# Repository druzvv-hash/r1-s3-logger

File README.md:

## 2026-10-23 — PowerBox now has its own R3 repository

Canonical project: [GLL R3 PowerBox](https://github.com/druzvv-hash/r3-powerbox),
branch **main**, local **C:/Projects/r3-powerbox**. Its README distinguishes Rev.A,
Rev.B candidate and user-reported physical checks. Existing hardware files were
copied byte-for-byte; PowerBox history was filtered with an original/new commit
map. Previously local RevB/manufacturing evidence is now tracked privately.
No circuit change, new hardware test or manufacturing approval is implied.
The old r3-powerbox-routing worktree and R1 branch remain historical references;
do not start new PowerBox development there. This supersedes older location and
local-only status below. See the new repository's docs/MIGRATION_2026-10-23.md.

<!-- External project memory audit - 2026-10-23 -->
**Current technical handoff:** [NOTES](NOTES.md) · [WORK_REPORT](WORK_REPORT.md) ·
[evidence and open issues](docs/PROJECT_MEMORY.md). Read [AGENTS](AGENTS.md)
before work. Version/status text below may describe older milestones; the dated
memory entry distinguishes current source, reported deployment and untested work.

# R1-S3 Logger

**[Посібник екосистеми: схеми, підключення та інструкції](../lily-logger-r3/docs/manual/README.uk.md)** — актуальний спільний вхід для R3, R1, CANBox і Viewer.

**English** | [Українська](README.uk.md)

Rebuilding Logger R1 around **ESP32-S3 + INA228**. Current firmware: **PANEL v0.36-can-live-dev**, with USB/Wi-Fi Start/Stop controls, integer 1–300 Hz measurements with presets and manual input, a 30/60 FPS live chart and explicit draft/apply/save settings. Sessions flow through a PSRAM FIFO into checked block writes on microSD. The encoder remains a no-GPIO stub. [Recording guide](docs/P5_RECORDING.md).

CAN tab: shared live/CBX playback/finite transmit workspace, using CANBox USB or
Wi-Fi directly. BLE remains service-only. [CAN guide](../GLL%20CANBox/docs/CAN_WORKSPACE.uk.md).

INA228 averaging/conversion controls and 10/30/60 s chart navigation: [guide](docs/INA228_PANEL.md).
**R3 ecosystem:** saved authenticated association, boot reconnect, coarse RTC
correction while idle and optional remote Start/Stop through R3's `/ecosystem`
page are implemented and host-tested. A [bounded two-board bench passed](docs/ECOSYSTEM_ACCEPTANCE_2026-09-09.md)
for saved permissions, coarse RTC correction, selected control and reboot recovery. Save
time-only or explicitly enable recording permission. New files use CSV v2 with
static group/RTC provenance, preserving v1 reading. [Operator guide](docs/ECOSYSTEM_CONTROL.md).

**Device UI:** run [device_ui/start.cmd](device_ui/start.cmd) with the board on native USB (COM9 on this PC),
or join the logger's Wi-Fi AP and open 192.168.4.1. Credentials are shown in the USB
panel's Diagnostics tab. [Test-panel guide](docs/P4A_TEST_PANEL.md).

**SD files:** the **Файли SD** tab lists folders and downloads existing files through
USB or Wi-Fi, without removing the card. [File transfer guide](docs/SD_DOWNLOADS.md).
The scrolling explorer includes search, sorting and automatic full-folder loading.
[Measured rate/noise limits](docs/RATE_BENCHMARK.md) distinguish usable control from
the experimental recording ceiling; v0.22 adds explicit [1–300 Hz profiles](docs/MEASUREMENT_RATES.md) with visible speed/noise tradeoffs.

## Hardware

- ESP32-S3-WROOM-2-N32R16V (reported marking MCN32R16V): 32 MB Octal Flash, 16 MB Octal PSRAM.
- Shared I²C bus: SDA GPIO8, SCL GPIO9, 100 kHz; INA228 `0x40`, SH1106G 128×64 OLED `0x3C`, 24C32 EEPROM `0x50`, DS3231 RTC `0x68`.
- SPI SD: CS GPIO10, MOSI GPIO11, SCK GPIO12, MISO GPIO13.
- INA228 ALERT: GPIO14. External shunt: owner-confirmed 60 mV / 400 A (150 microohms).
- OLED rotation: 180°. The current bench uses direct ESP32-S3 USB Serial/JTAG on COM9.

See the [pin map](hardware/pinmap.md). Board revision and SD module circuitry remain to be recorded.

Selected local control: [Bourns PEC11R-4220F-S0024](hardware/encoder.md), not yet installed. Physical and web controls will share one device state.

## Verified status

| Component | Result |
|---|---|
| Flash / PSRAM | Detected; no memory stress test performed |
| I²C | Four expected addresses responding in repeated scans without bus errors |
| SD | 10 MHz write, close, remount and exact readback PASS; output files checked on a PC |
| OLED | SH1106G 128×64 image and 180° rotation confirmed by the owner |
| EEPROM | Owner confirmed EEP PASS: backup, sample write, restore and full-image comparison |
| RTC | Browser UTC synchronization verified; OSF=0, tick PASS; retention checked after owner-reported power disconnection |
| INA228 | Fresh ADC and owner-reported voltage comparison established; independent current calibration and active ALERT pending |

Native USB flashing, full-image verification and console operation are confirmed. Use direct USB going forward; the cause of intermittent CP210x failures remains unproven.

## VS Code / PlatformIO

Open the repository root in VS Code with PlatformIO IDE installed. Dependencies are pinned to `espressif32@6.12.0` (Arduino 2.0.17), `Adafruit SH110X@2.1.12` and `NimBLE-Arduino@1.4.3`.

```sh
pio run
```

The default environment is `esp32-s3-usb`: direct USB Serial/JTAG with the console enabled. This R1 is COM9; confirm device identity before flashing (CANBox is COM11). Close the UI bridge / Serial Monitor before uploading. Port numbers may change on another PC.

```sh
pio run -e esp32-s3-usb -t upload --upload-port COM9
pio device monitor -e esp32-s3-usb -p COM9
```

`esp32-s3-uart-manual` retains the BOOT + RESET fallback (manual RESET after upload). `esp32-s3` retains the old UART profile; native USB is the normal workflow. The explicit `esp32-s3-service` build enables the original SD/EEPROM write tests; ordinary builds exclude them.

## Current behavior and migration

Normal boot reads the SD root and checks two complete EEPROM reads, then displays live voltage/current. It creates no SD test files and writes no EEPROM patterns. `SD READ / SAVED` indicates readable SD and matching persisted settings; UNSAVED means explicit saving is needed. The explicit [RTC sync](docs/rtc-sync.md) command remains available; saved R3 enrollment also permits automatic fresh RTC correction while idle. INA228 uses timed 1–300 Hz acquisition. Explicit START creates a session; STOP drains, verifies and closes it before publishing the CSV.

[3 A / 3 V load acceptance](docs/LOAD_TEST_2026-09-08.md): all three rates passed without missed samples or I2C errors; 40 verified USB downloads passed alongside 100 Hz acquisition. v0.17 fixes delayed panel-state publication found during these tests.

The [PSRAM FIFO and block-buffer foundation](docs/BUFFERING_AND_REUSE.md) is implemented and host-tested. Boot reserves the configured sample budget in PSRAM plus 8 KiB internal SD staging; the recorder now uses these buffers after explicit Start. P4a now has a working web test panel on core 0 and a hardware command owner on core 1. [P4b live acquisition](docs/P4B_LIVE_ACQUISITION.md) now uses timed INA conversions, chunked OLED transfers and batched PSRAM preview. [P5 session files](docs/P5_RECORDING.md) are implemented; local menus remain.

[P0 baseline and backup evidence](docs/P0_BASELINE.md). P1 contracts: [settings/EEPROM](docs/CONFIG_SCHEMA.md), [self-contained CSV](docs/FILE_FORMAT.md), [viewer compatibility](docs/VIEWER_COMPATIBILITY.md). Run host checks with `python -m unittest discover -s tests -v` (Python 3.10+; firmware-core tests also need a native C++ compiler). P2 viewer is implemented: launch `viewer/start.cmd` or `python viewer/server.py`. [Viewer guide](viewer/README.md) · [P2 results](docs/P2_VIEWER.md). P3 settings/EEPROM are implemented: [commands and evidence](docs/P3_SETTINGS.md). P5 connects acquisition to session recording, checkpoints and rotation; physical acceptance and limits are in the recording guide. The owner deferred remaining R5 analysis/plugins until real logger files exist. The current viewer is a data-reading foundation, not a feature-complete R5 replacement.

## Repository guide

- [BLE link controls](docs/BLE_LINK.md): authenticated pairing and explicit saved permission through **BLE · R3**. The [v0.24 two-board bench](docs/ECOSYSTEM_ACCEPTANCE_2026-09-09.md) verifies control and recovery within documented limits; extended qualification and the earlier 300 Hz signal-quality question remain open.
- [Ecosystem control](docs/ECOSYSTEM_CONTROL.md): time-only/remote permission, ON/OFF/FORGET, boot RTC correction and selected R3 control.
- [Ecosystem synchronization](docs/ECOSYSTEM_TIME_SYNC.md): R3 / R1-S3 / CAN architecture; [CSV v2](docs/FILE_FORMAT_V2.md) has static provenance, while precise sample alignment and the CAN adapter remain pending.
- [firmware/](firmware/README.md): Arduino test firmware and GPIO constants.
- [hardware/](hardware/README.md): hardware notes and pin map.
- [Bring-up plan and results](docs/bring-up.md).
- [SD serial evidence](docs/sd-test-v0.2-serial.txt).
- [Project context](docs/project-context-review.md): relevant findings from earlier logger work.
- [Ukrainian owner notes](docs/uk/README.md): historical bench notes and local workspace review.

See the staged plan below for remaining acquisition, calibration, ALERT and recording acceptance work.

Legacy recovery: [R1 firmware and viewer review](docs/legacy-r1-analysis.md).

- [Migration journal](docs/R1_MIGRATION.md): migration stages, decisions and dated hardware evidence.

- [Engineering plan](docs/R1_S3_PLAN.md): architecture, EEPROM, self-contained recording and cross-version viewer roadmap.

## CANBox fallback (experimental)

The direct CANBox control adapter and panel are implemented in the working tree.
R1 flashing and the two-board BLE acceptance are pending a manual BOOT/RESET.
See [CANBox fallback status and procedure](docs/CANBOX_FALLBACK.md).

The owner confirmed that the R1 SD card was removed during the CANBox bench. The observed SD FAIL therefore does not establish an SD fault; recheck after reinsertion.

Deployed update: **0.28-canbox-dev** adds an always-visible CANBox status and controls, including unknown/offline and pending states. Native USB deployment and live CANBox readiness/authorization verified.

## CANBox clock update 0.29

Deployed: the connected R1 supplies its valid, fresh RTC calendar to CANBox.
START requires clock_synced; STOP remains available. Live synchronization
passed; the new SD-file acceptance test awaits card reinsertion in CANBox.
See `C:\Projects\GLL CANBox\docs\CLOCK_SYNC_2026-09-15.uk.md`.

**CANBox + R1:** [Спільний запис / linked Start and Stop](docs/LINKED_RECORDING.uk.md) — перемикач біля старту CANBox, одна група сесій, підтверджений стан обох пристроїв.

Wi-Fi firmware updates: [Browser OTA](docs/OTA.md).

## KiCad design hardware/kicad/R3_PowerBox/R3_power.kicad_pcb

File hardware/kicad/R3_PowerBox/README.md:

# R3 PowerBox

Editable KiCad 10 project for the R3 power module. The schematic uses one root
page and ten functional child sheets so battery/BMS, charger/power-path,
user system-power control, primary converters, isolation, LDOs, INA bipolar power and connectors can be
reviewed independently.

## Open

Open `R3_power.kicad_pro` in KiCad 10. The canonical schematic is
`R3_power.kicad_sch`; the PCB file is `R3_power.kicad_pcb`.

## Directory layout

- `R3_power.kicad_pro` — KiCad project settings;
- `R3_power.kicad_sch` — power schematic;
- `R3_power.kicad_pcb` — PCB workspace;
- `libraries/` — project-local symbols and source libraries;
- `footprints/` — project-local provisional footprints;
- `docs/` — design decisions, checks, and transfer notes;
- `bom/` — KiCad-exported BOM plus sourcing/review notes;
- `legacy/` — read-only KiCad 5 source retained for migration reference;
- `tools/` — reproducible schematic generator and its setup notes;
- `manufacturing/` — release outputs only after schematic/PCB review;
- `reports/` — ERC/DRC reports generated during checks.

## Safety and design status

- The board is a unified 2S Li-ion power-management design. The preliminary
  system range is 6.0-8.4 V; there is no intermediate 2S-to-9 V converter.
- J1 is retained as a protected service/bench charger input. USB-C is the
  primary external input; STUSB4500 implements 5/9/12 V negotiation with
  12 V/2 A preferred and a boot-safe 0.50 A charger default.
- `DGND` and `GND_ISO` are separate galvanic domains and must never be joined.
- SW1/Q4 disconnect only `VSYS_MAIN`; BMS, PD and charging remain active while
  R3 is off. SW2 is the separate QON ship/wake/service control.
- The present files are an engineering prototype, not a manufacturing release.
- Q2/Q3, F1/F2/F3 and the dual-NTC strategy are selected for Rev.A. Battery
  chemistry/configuration, hot-current validation and PD NVM compliance remain
  open before ordering a PCB.
- The PCB contains a 160 x 80 mm outline, four spatial zones, an isolation
  keepout on all four copper layers, six NPTH M3 mounting holes, optional
  primary/isolated B2B headers and final pre-routing component placement. It
  has no routing or vias.
- KiCad ERC has zero errors. Remaining generator-related warnings and the visual
  review limitations are recorded in `docs/VERIFICATION.md`.

Start with [the current power review](R3_POWER_REVIEW.md) and
[battery architecture](R3_BATTERY_POWER_ARCHITECTURE.md), then see the compact
[design notes](docs/R3_power_module_design.md) and
[verification status](docs/VERIFICATION.md). Placement images are in
`reports/R3_power_preliminary_placement.png` and
`reports/R3_power_zone_isolation_annotated.png`; mechanical stack dimensions
and views are in [the B2B interface note](docs/R3_BOARD_TO_BOARD_INTERFACE.md).

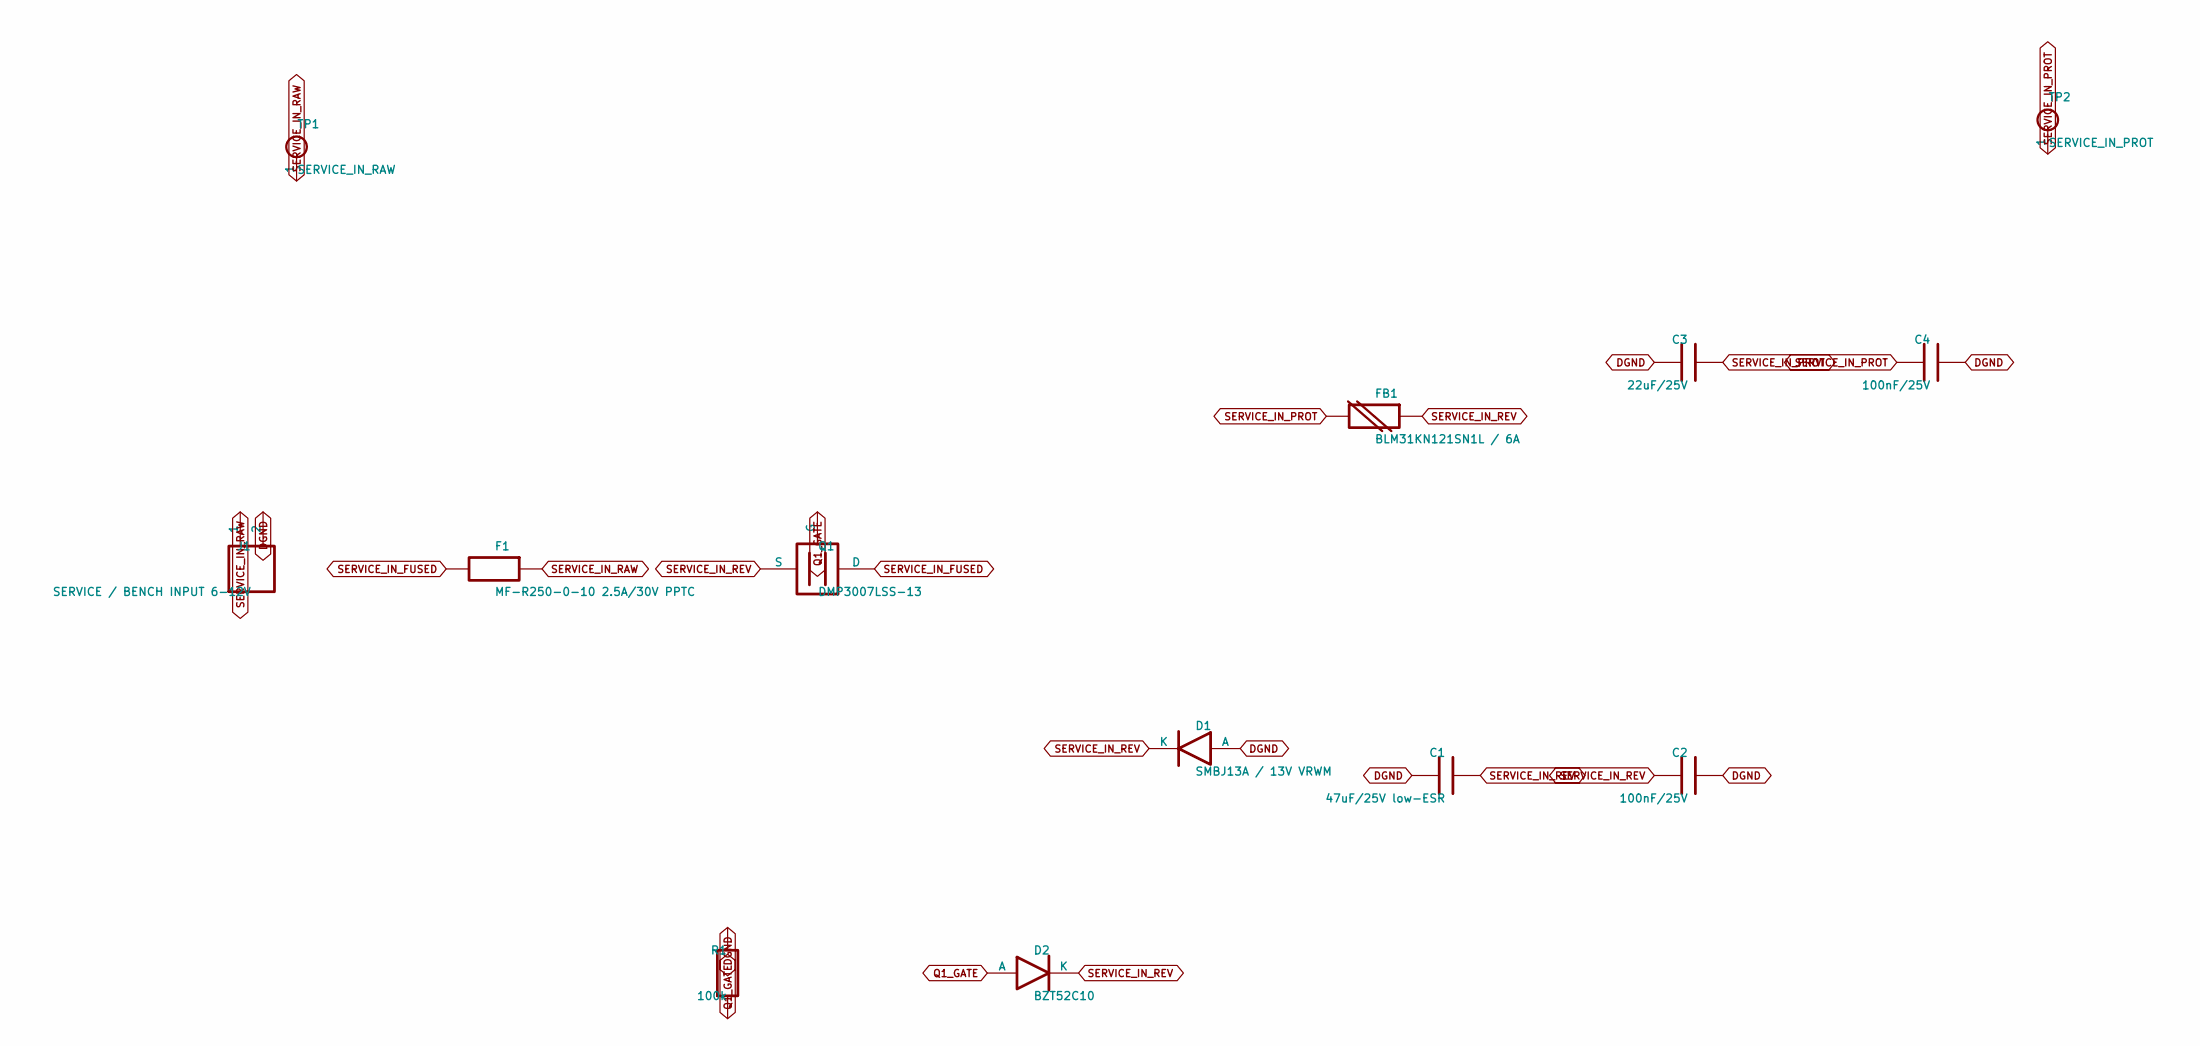
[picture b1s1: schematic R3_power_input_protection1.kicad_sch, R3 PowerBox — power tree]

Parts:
C1: 47uF/25V low-ESR; CP_Elec_6.3x5.8
C2, C4: 100nF/25V; C_0603_1608Metric
C3: 22uF/25V; C_1206_3216Metric
D1: SMBJ13A / 13V VRWM; D_SMB
D2: BZT52C10; D_SOD-123
F1: MF-R250-0-10 2.5A/30V PPTC; Fuse_PTC_MF-R250
FB1: BLM31KN121SN1L / 6A; L_1206_3216Metric_Pad1.22x1.90mm_HandSolder
J1: SERVICE / BENCH INPUT 6-12V; Molex_Micro-Fit_3.0_43650-0200_1x02_P3.00mm_Horizontal
Q1: DMP3007LSS-13; DMP3007LSS_SO8_LOGICAL
R1: 100k; R_0603_1608Metric
TP1: SERVICE_IN_RAW; TestPoint_Plated_Hole_D2.0mm
TP2: SERVICE_IN_PROT; TestPoint_Plated_Hole_D2.0mm

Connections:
DGND: C1.2, C2.2, C3.2, C4.2, D1.2 (A), J1.2, R1.2; also elsewhere on the board
Q1_GATE: D2.2 (A), Q1.1 (G), R1.1
SERVICE_IN_FUSED: F1.2, Q1.3 (D)
SERVICE_IN_PROT: C3.1, C4.1, FB1.2, TP2.1; also elsewhere on the board
SERVICE_IN_RAW: F1.1, J1.1, TP1.1
SERVICE_IN_REV: C1.1, C2.1, D1.1 (K), D2.1 (K), FB1.1, Q1.2 (S)

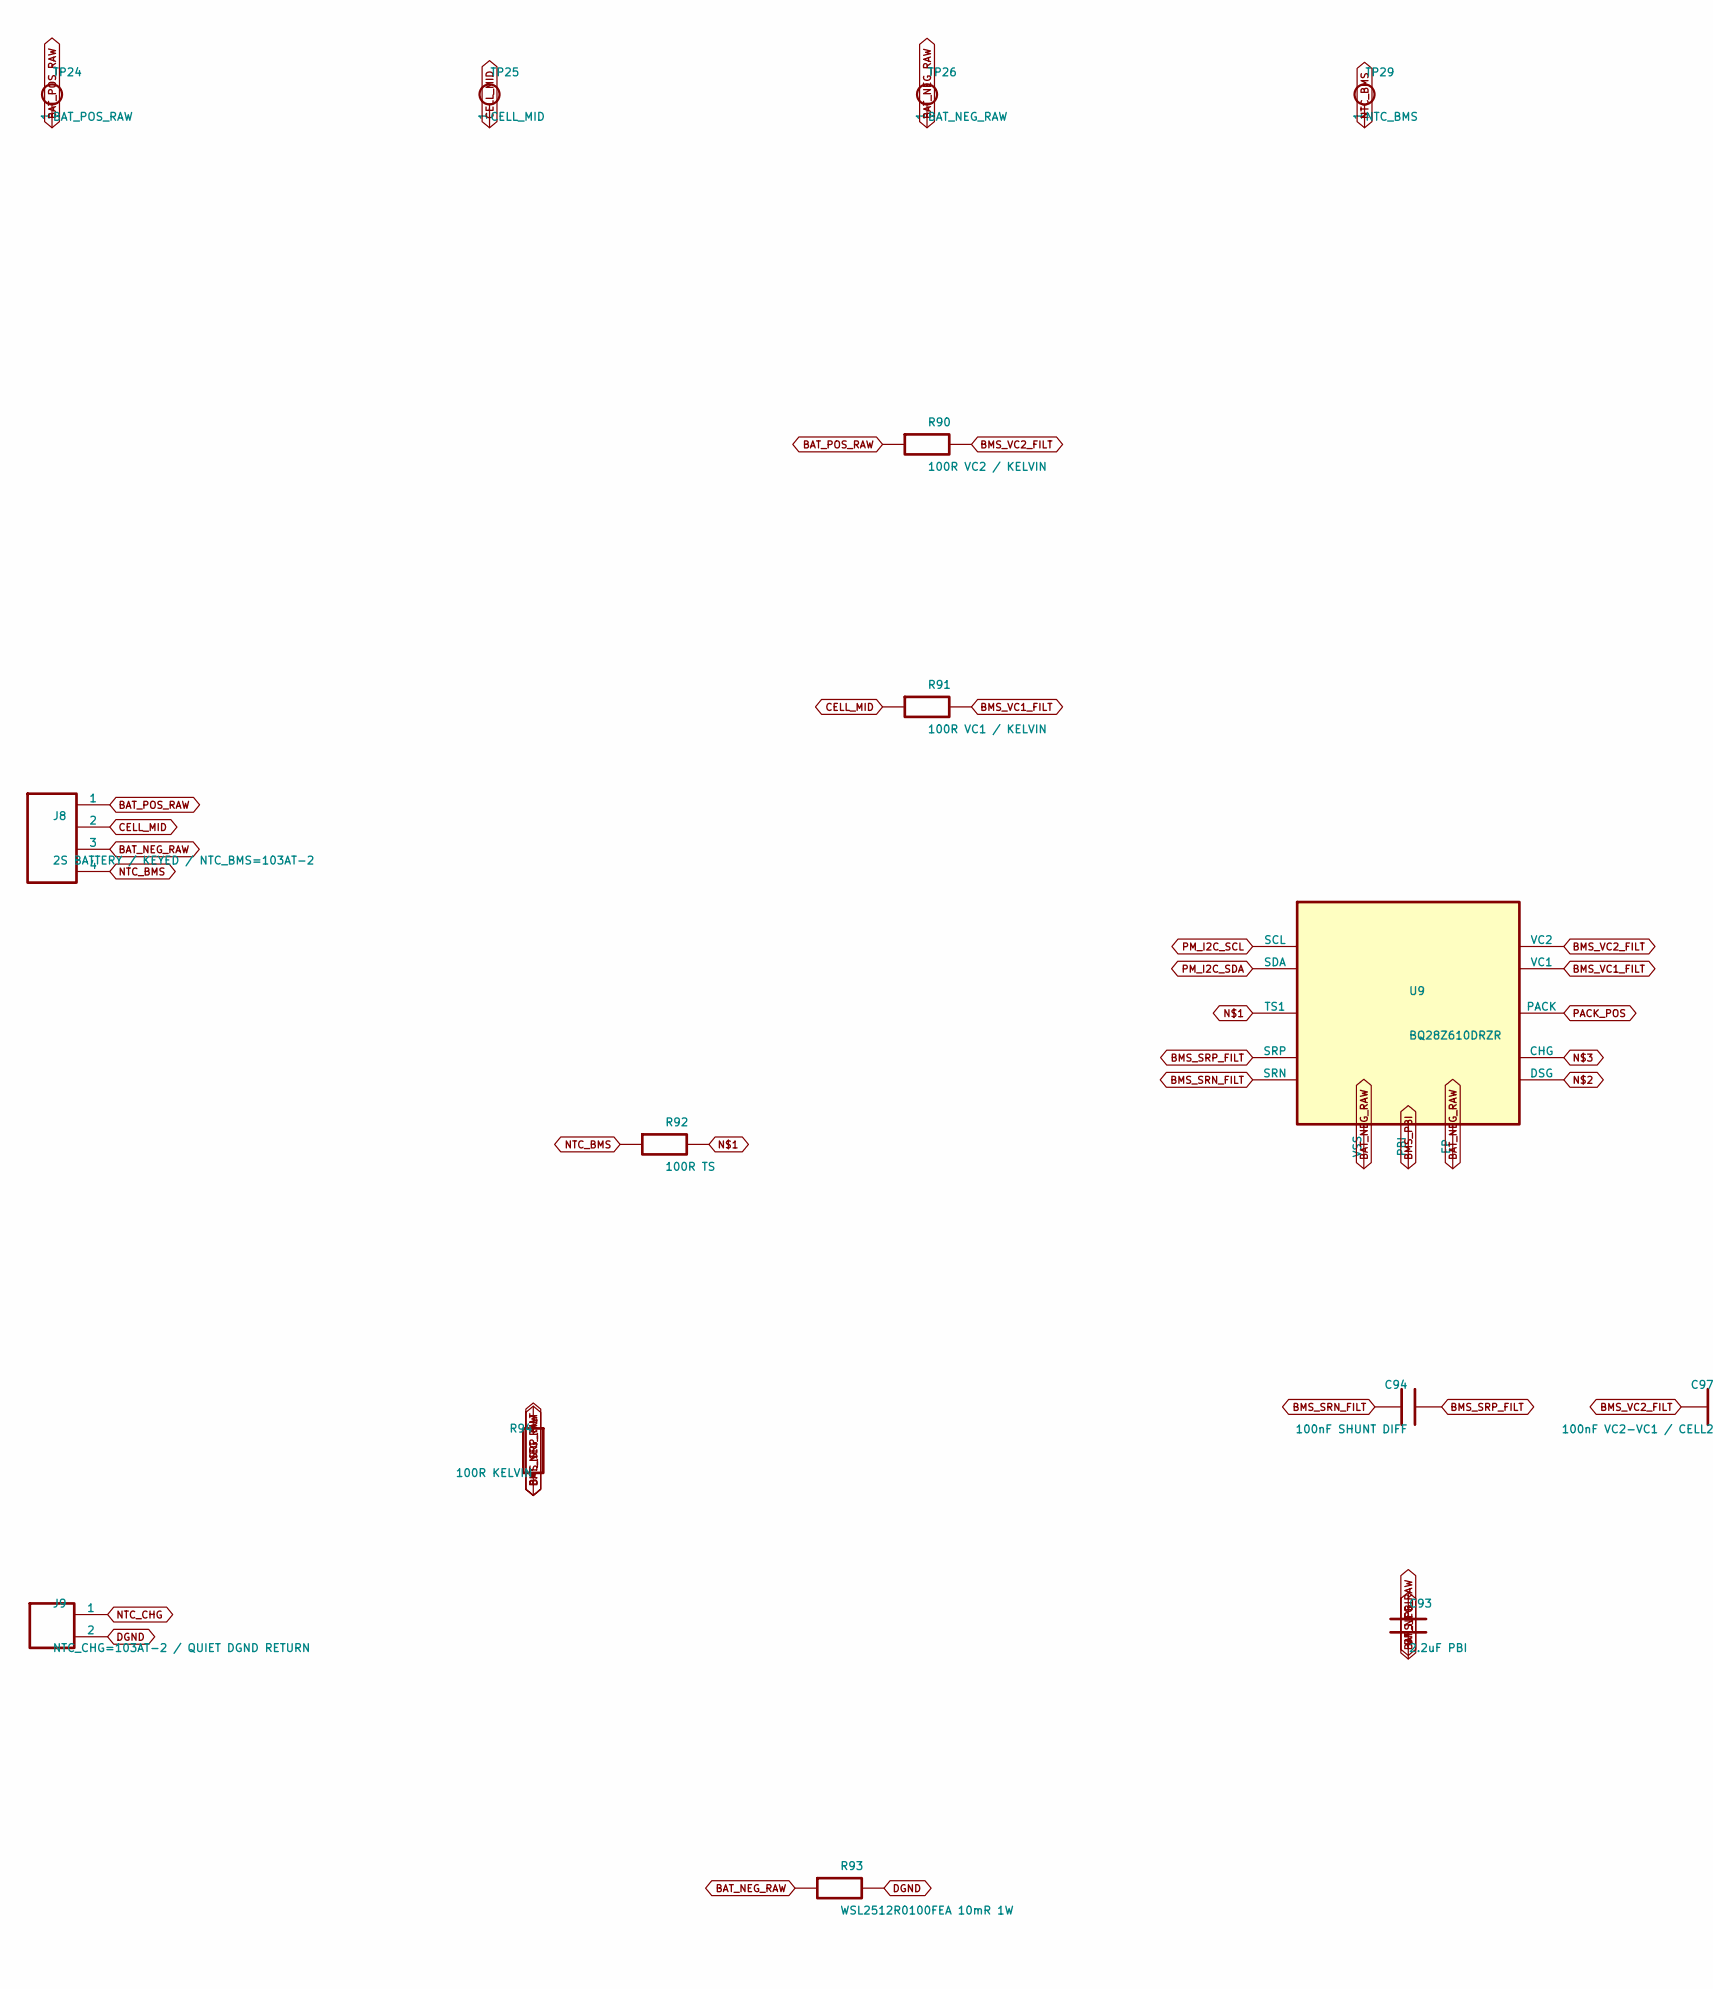
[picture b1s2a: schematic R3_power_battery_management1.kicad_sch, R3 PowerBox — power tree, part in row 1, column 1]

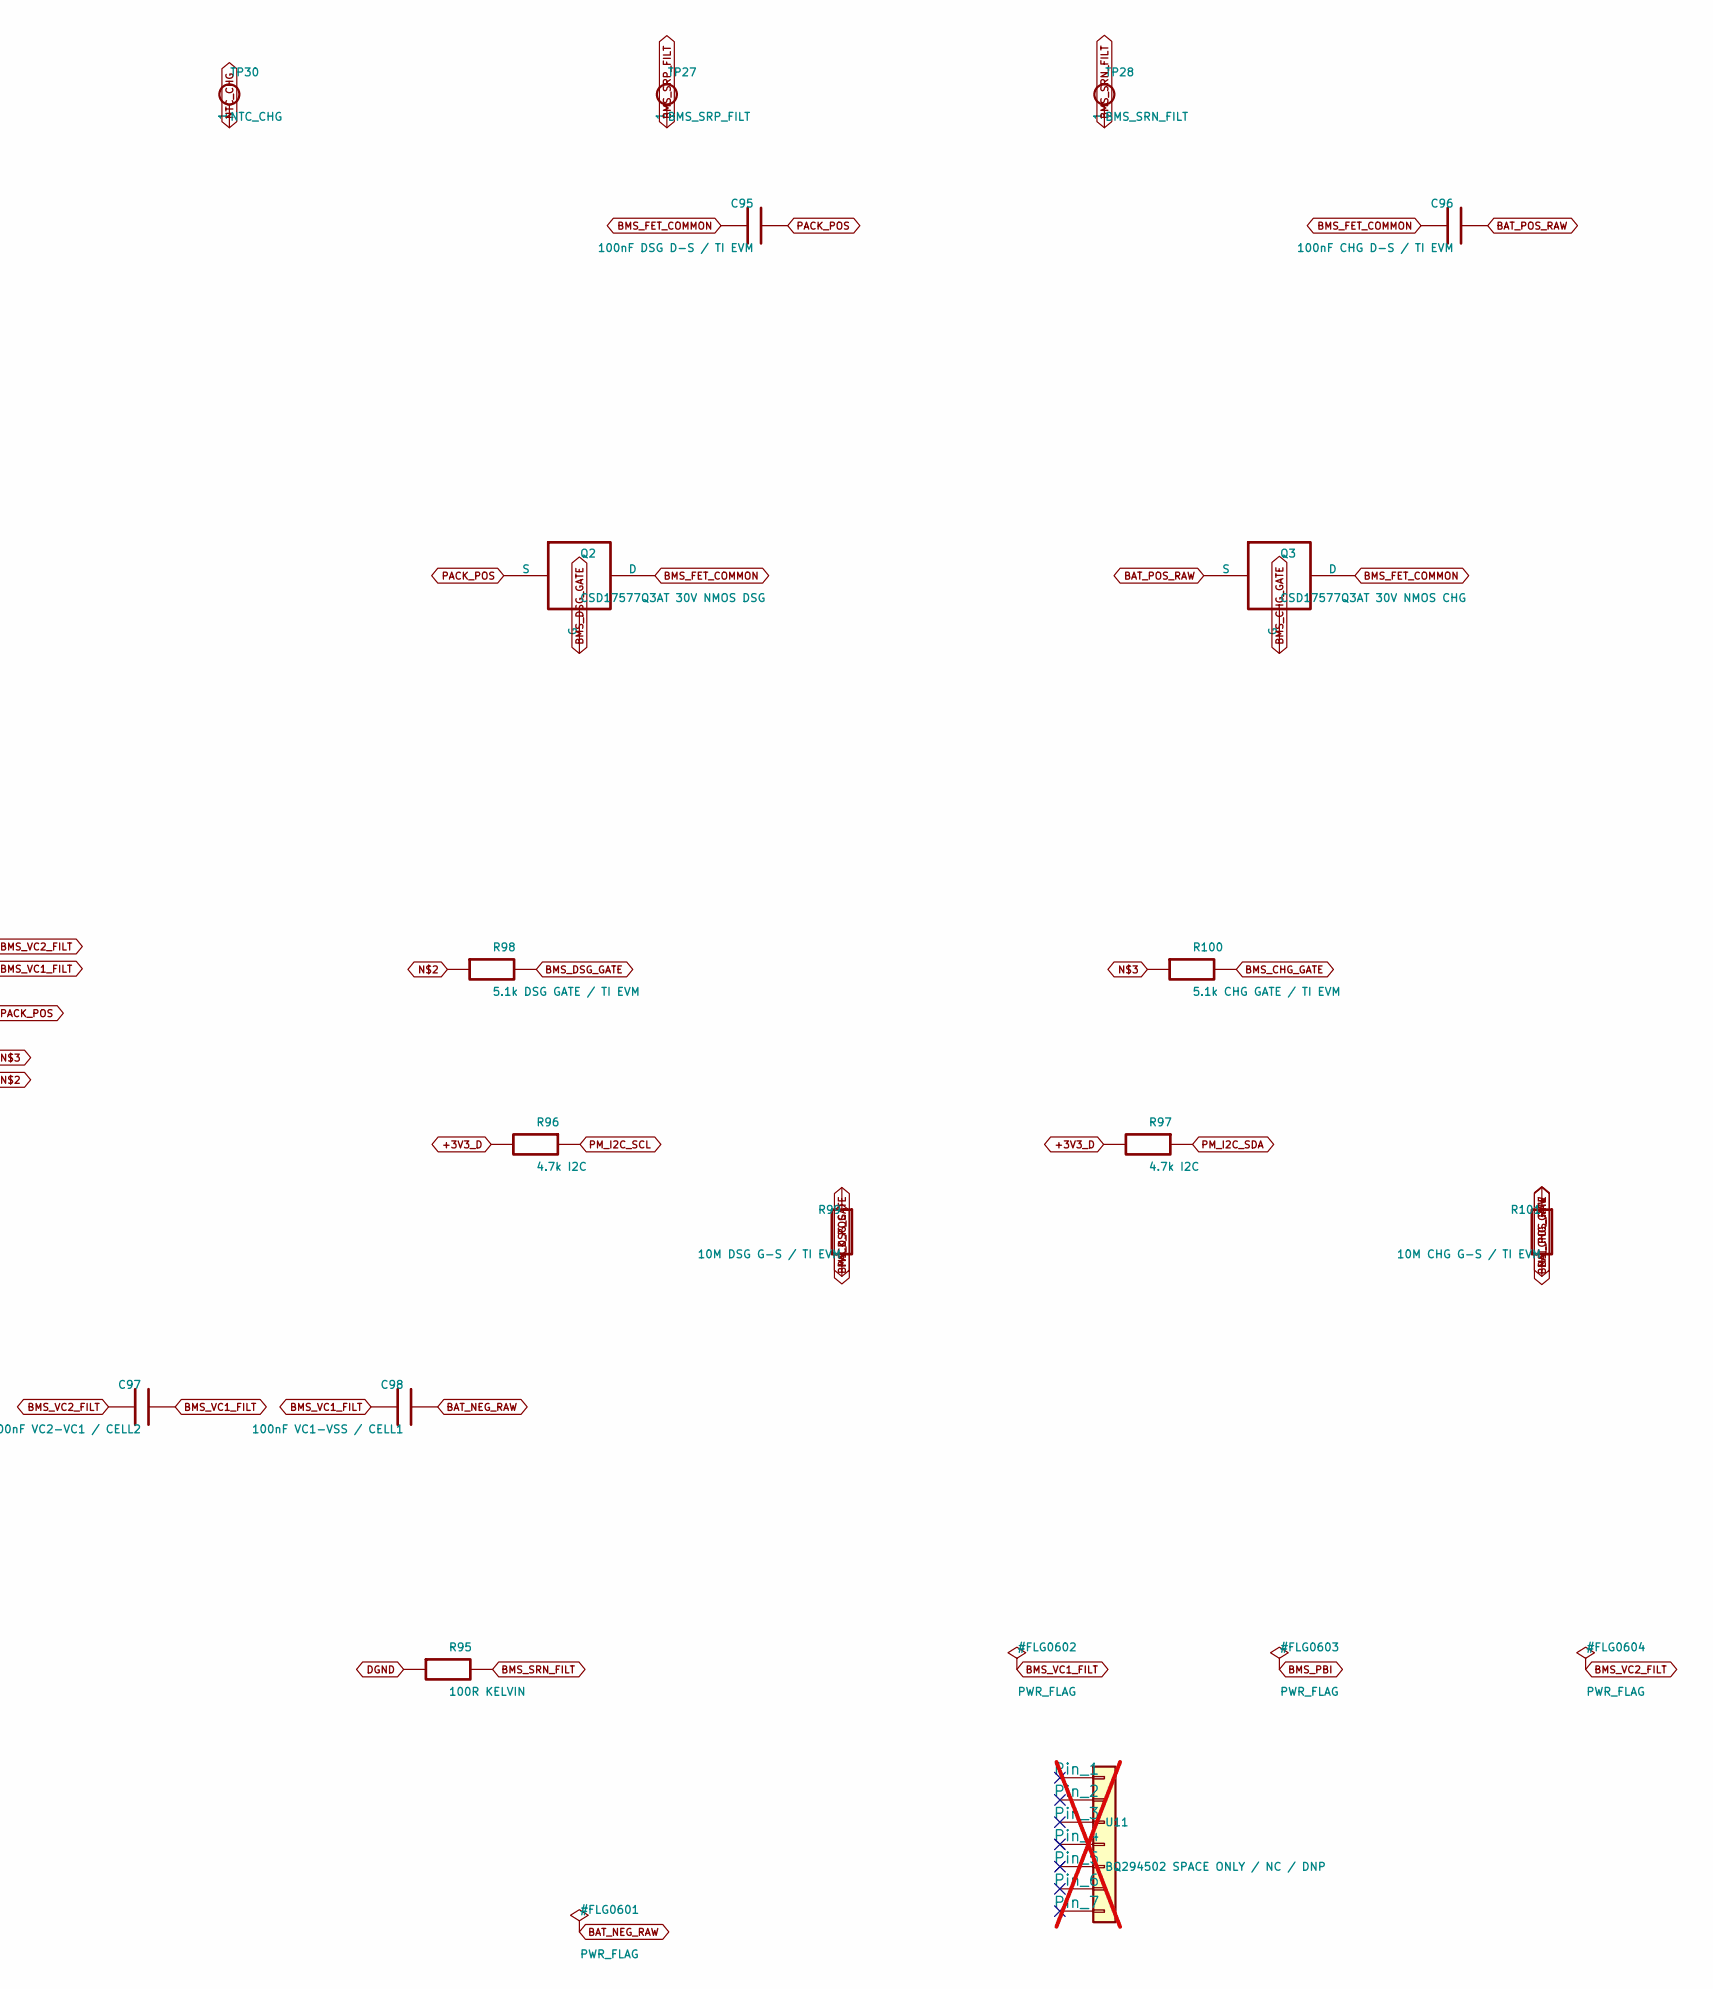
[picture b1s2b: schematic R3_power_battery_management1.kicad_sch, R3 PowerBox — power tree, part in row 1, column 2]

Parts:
C93: 2.2uF PBI; C_0603_1608Metric
C94: 100nF SHUNT DIFF; C_0603_1608Metric
C95: 100nF DSG D-S / TI EVM; C_0603_1608Metric
C96: 100nF CHG D-S / TI EVM; C_0603_1608Metric
C97: 100nF VC2-VC1 / CELL2; C_0603_1608Metric
C98: 100nF VC1-VSS / CELL1; C_0603_1608Metric
J8: 2S BATTERY / KEYED / NTC_BMS=103AT-2; Molex_Micro-Fit_3.0_43650-0400_1x04_P3.00mm_Horizontal
J9: NTC_CHG=103AT-2 / QUIET DGND RETURN; Molex_Micro-Fit_3.0_43650-0200_1x02_P3.00mm_Horizontal
Q2: CSD17577Q3AT 30V NMOS DSG; CSD17577Q3A_VSON-8_3.3x3.3mm
Q3: CSD17577Q3AT 30V NMOS CHG; CSD17577Q3A_VSON-8_3.3x3.3mm
R90: 100R VC2 / KELVIN; R_0603_1608Metric
R91: 100R VC1 / KELVIN; R_0603_1608Metric
R92: 100R TS; R_0603_1608Metric
R93: WSL2512R0100FEA 10mR 1W; R_2512_6332Metric_Pad1.40x3.35mm_HandSolder
R94, R95: 100R KELVIN; R_0603_1608Metric
R96, R97: 4.7k I2C; R_0603_1608Metric
R98: 5.1k DSG GATE / TI EVM; R_0603_1608Metric
R99: 10M DSG G-S / TI EVM; R_0603_1608Metric
R100: 5.1k CHG GATE / TI EVM; R_0603_1608Metric
R101: 10M CHG G-S / TI EVM; R_0603_1608Metric
TP24: BAT_POS_RAW; TestPoint_Plated_Hole_D2.0mm
TP25: CELL_MID; TestPoint_Plated_Hole_D2.0mm
TP26: BAT_NEG_RAW; TestPoint_Plated_Hole_D2.0mm
TP27: BMS_SRP_FILT; TestPoint_Pad_D1.0mm
TP28: BMS_SRN_FILT; TestPoint_Pad_D1.0mm
TP29: NTC_BMS; TestPoint_Plated_Hole_D2.0mm
TP30: NTC_CHG; TestPoint_Plated_Hole_D2.0mm
U9: BQ28Z610DRZR; Texas_DRZ0012A_VSON-12
U11: BQ294502 SPACE ONLY / NC / DNP; WSON-6-1EP_2x2mm_P0.65mm_EP1x1.6mm; not fitted

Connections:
+3V3_D: R96.2, R97.2; also elsewhere on the board
BAT_NEG_RAW: C93.2, C98.2, J8.3, R93.1, R94.1, TP26.1, U9.1 (VSS), U9.13 (EP)
BAT_POS_RAW: C96.2, J8.1, Q3.2 (S), R90.1, R101.2, TP24.1
BMS_CHG_GATE: Q3.1 (G), R100.2, R101.1
BMS_DSG_GATE: Q2.1 (G), R98.2, R99.1
BMS_FET_COMMON: C95.2, C96.1, Q2.3 (D), Q3.3 (D)
BMS_PBI: C93.1, U9.10 (PBI)
BMS_SRN_FILT: C94.2, R95.2, TP28.1, U9.2 (SRN)
BMS_SRP_FILT: C94.1, R94.2, TP27.1, U9.3 (SRP)
BMS_VC1_FILT: C97.2, C98.1, R91.2, U9.12 (VC1)
BMS_VC2_FILT: C97.1, R90.2, U9.11 (VC2)
CELL_MID: J8.2, R91.1, TP25.1
DGND: J9.2, R93.2, R95.1; also elsewhere on the board
unnamed: R92.2, U9.4 (TS1)
unnamed: R98.1, U9.7 (DSG)
unnamed: R100.1, U9.9 (CHG)
NTC_BMS: J8.4, R92.1, TP29.1
NTC_CHG: J9.1, TP30.1; also elsewhere on the board
PACK_POS: C95.1, Q2.2 (S), R99.2, U9.8 (PACK); also elsewhere on the board
PM_I2C_SCL: R96.1, U9.5 (SCL); also elsewhere on the board
PM_I2C_SDA: R97.1, U9.6 (SDA); also elsewhere on the board
